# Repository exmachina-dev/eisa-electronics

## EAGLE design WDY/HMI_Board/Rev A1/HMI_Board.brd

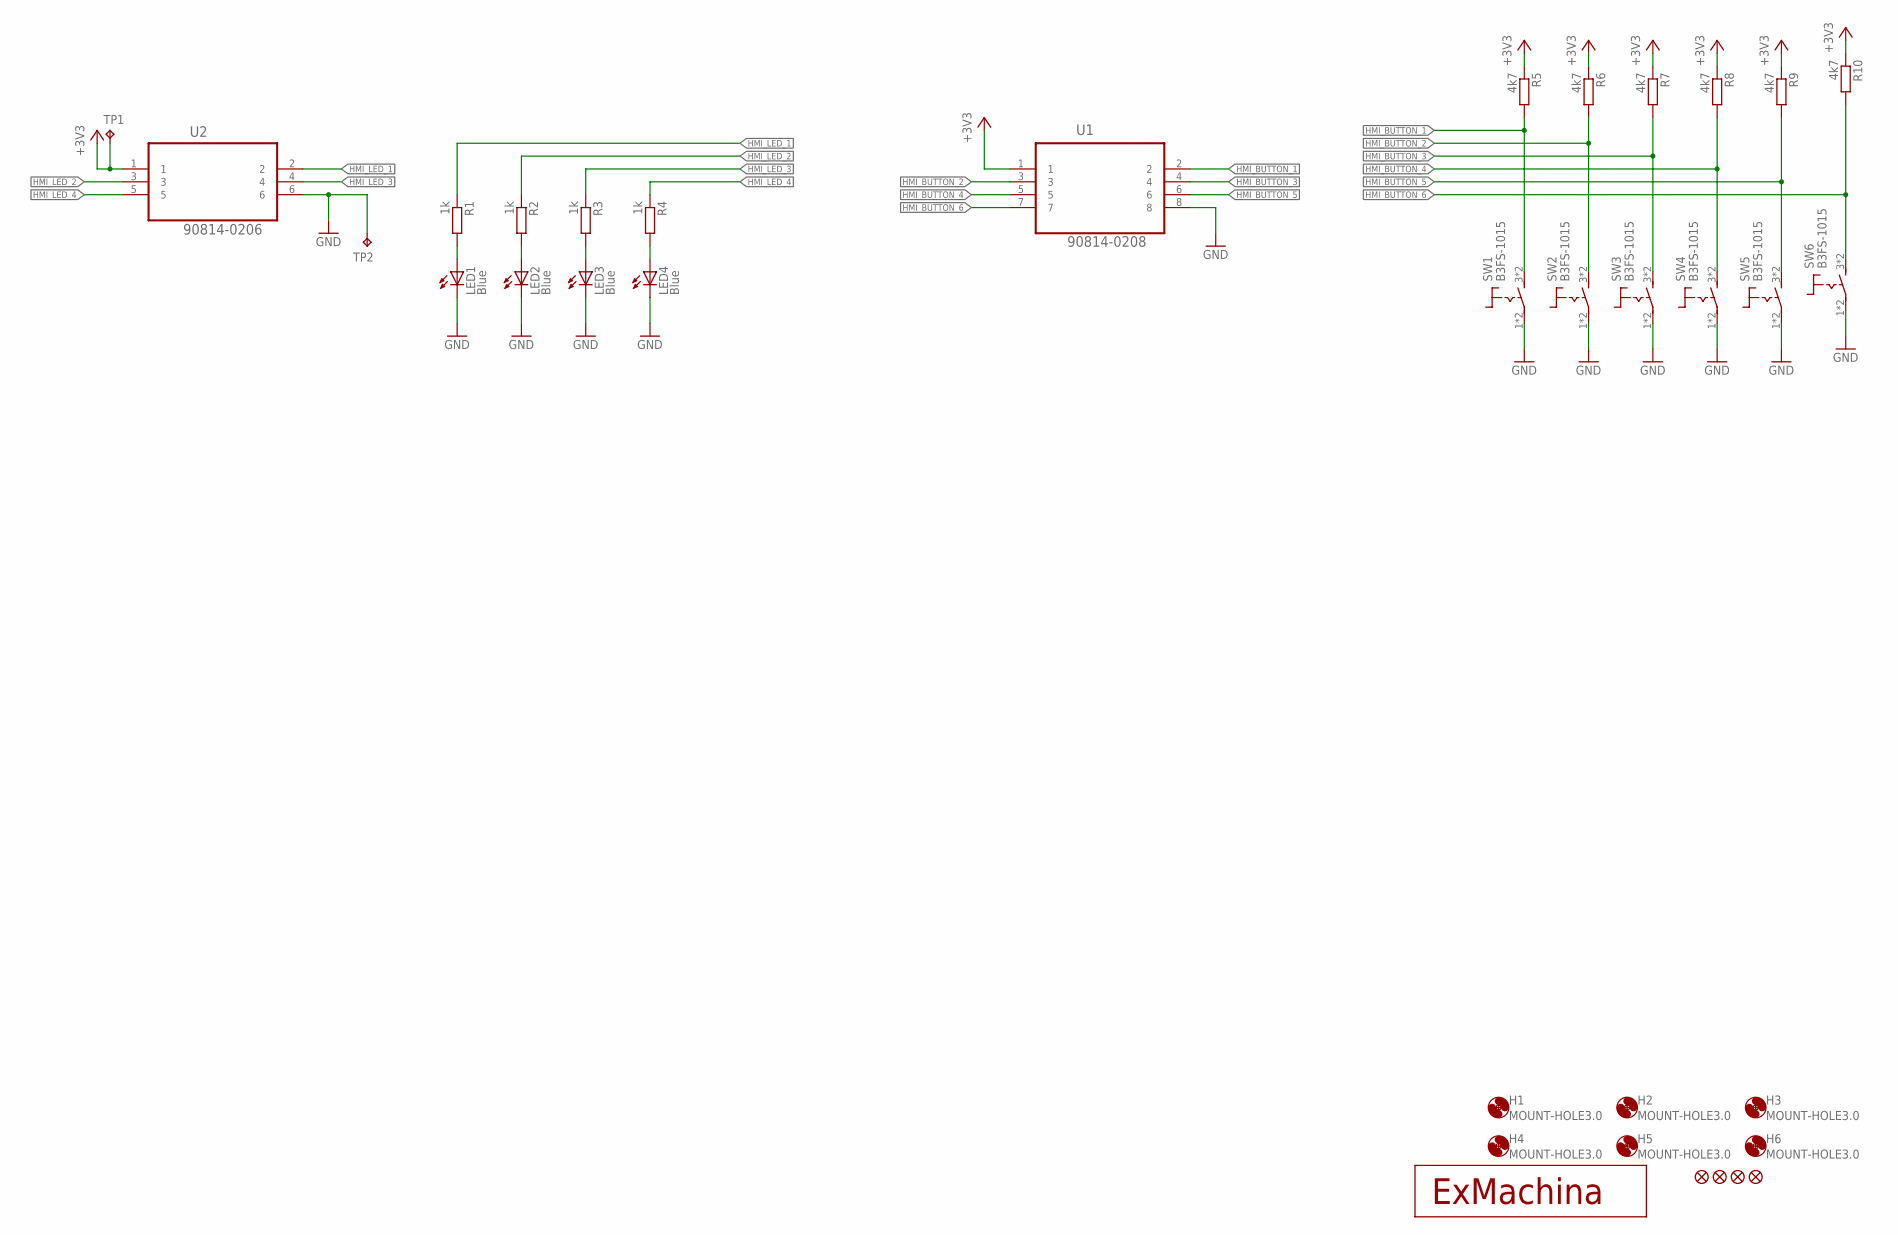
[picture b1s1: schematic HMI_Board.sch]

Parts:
H1, H2, H3, H4, H5, H6: MOUNT-HOLE3.0; 3,0
JP1, JP2, JP3, JP4: FIDUCIAL1X2; FIDUCIAL-1X2
LED1, LED2, LED3, LED4: Blue; SML0603
R1, R2, R3, R4: 1k; R0603
R5, R6, R7, R8, R9, R10: 4k7; R0603
SW1, SW2, SW3, SW4, SW5, SW6: B3FS-1015; B3FS
TP1, TP2: TPB2,54; B2,54
U1: 90814-0208; MOLEX_90814-0208
U2: 90814-0206; MOLEX_90814-0206
U$1: EXMACHINA-LOGO-NAME; EXM-LOGO-BASELINE

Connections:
+3V3: R5.1, R6.1, R7.1, R8.1, R9.1, R10.1, TP1.TP, U1.1, U2.1
GND: LED1.C, LED2.C, LED3.C, LED4.C, SW1.1 (2), SW1.2, SW2.1 (2), SW2.2, SW3.1 (2), SW3.2, SW4.1 (2), SW4.2, SW5.1 (2), SW5.2, SW6.1 (2), SW6.2, TP2.TP, U1.8, U2.6
HMI_BUTTON_1: R5.2, SW1.3 (1), SW1.4 (1), U1.2
HMI_BUTTON_2: R6.2, SW2.3 (1), SW2.4 (1), U1.3
HMI_BUTTON_3: R7.2, SW3.3 (1), SW3.4 (1), U1.4
HMI_BUTTON_4: R8.2, SW4.3 (1), SW4.4 (1), U1.5
HMI_BUTTON_5: R9.2, SW5.3 (1), SW5.4 (1), U1.6
HMI_BUTTON_6: R10.2, SW6.3 (1), SW6.4 (1), U1.7
HMI_LED_1: R1.1, U2.2
HMI_LED_2: R2.1, U2.3
HMI_LED_3: R3.1, U2.4
HMI_LED_4: R4.1, U2.5
unnamed: LED1.A, R1.2
unnamed: LED2.A, R2.2
unnamed: LED3.A, R3.2
unnamed: LED4.A, R4.2

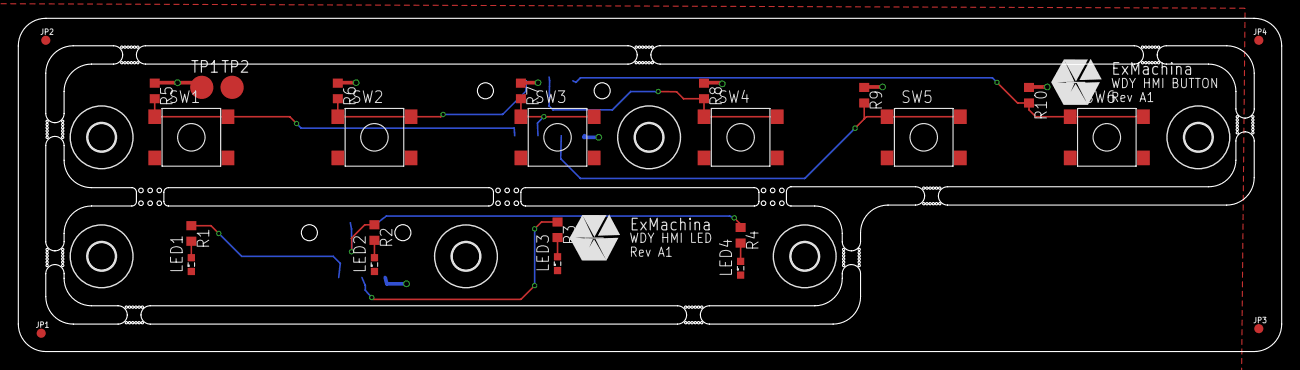
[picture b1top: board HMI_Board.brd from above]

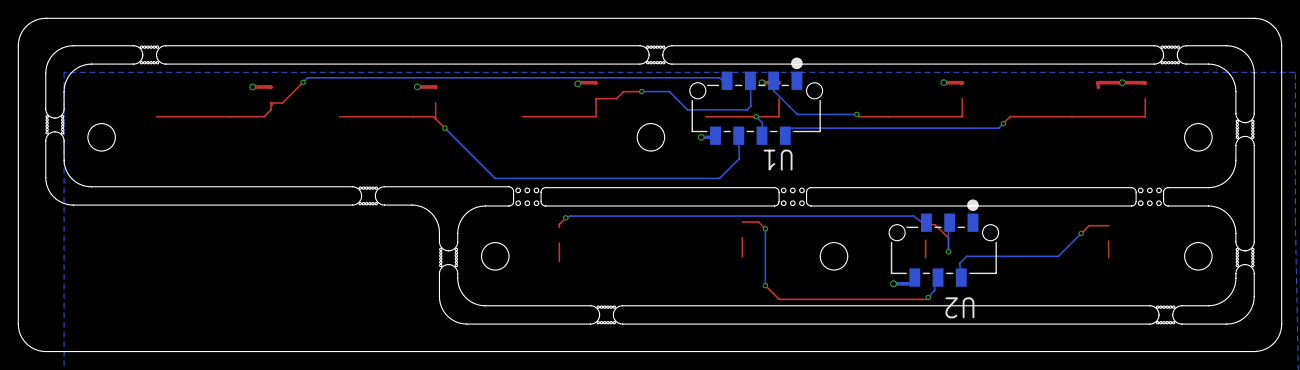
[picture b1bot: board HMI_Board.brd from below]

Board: 2 copper layers, 138.0 x 36.4 mm, 36 parts (2 on the bottom side), 16 nets.

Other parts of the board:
U$2: EXMACHINA-LOGO-NAME; EXM-LOGO-BASELINE

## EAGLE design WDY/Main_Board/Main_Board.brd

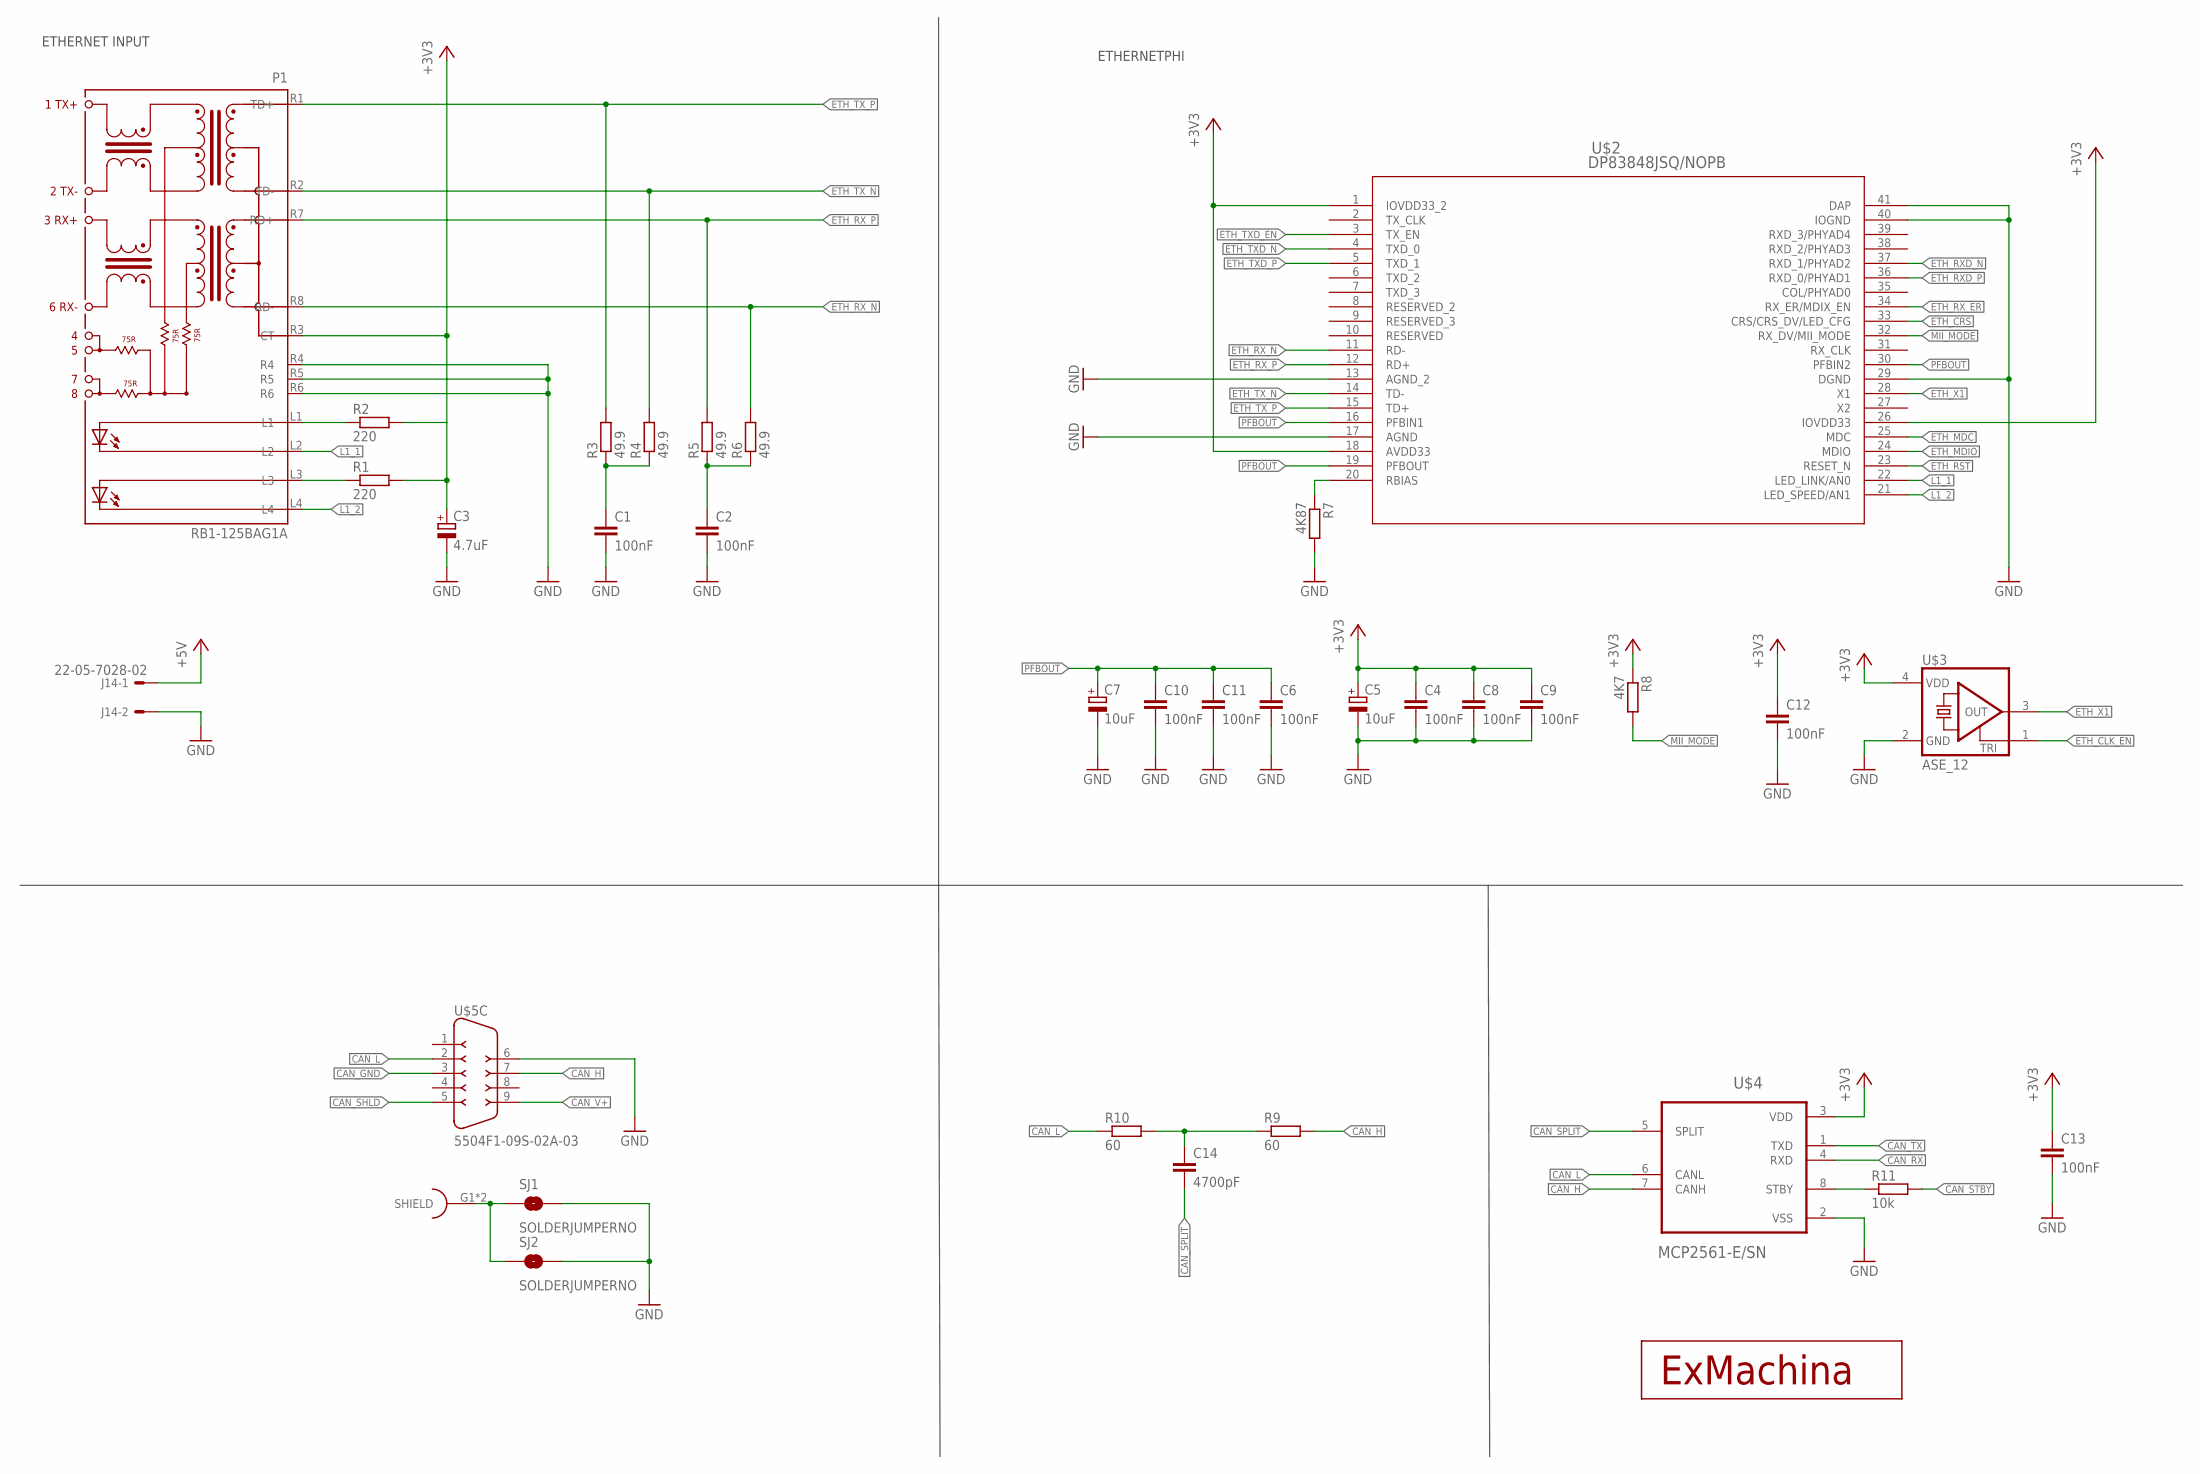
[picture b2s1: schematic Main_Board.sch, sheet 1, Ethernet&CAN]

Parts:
C1, C2, C4, C6, C8, C9, C10, C11, C12, C13: 100nF; C0603
C3: 4.7uF; CT3216
C5, C7: 10uF; CT3216
C14: 4700pF; C0603
J14: 22-05-7028-02; 7395-02
P1: RB1-125BAG1A; WIZNET_RB1-125BAG1A
R1, R2: 220; R0603
R3, R4, R5, R6: 49.9; R0603
R7: 4K87; R0603
R8: 4K7; R0603
R9, R10: 60; R0603
R11: 10k; R0603
SJ1, SJ2: SOLDERJUMPERNO; SJ_2S-NO
U$1: EXMACHINA-LOGO-NAME; EXM-LOGO-BASELINE
U$2: DP83848JSQ/NOPB; SQA40B
U$3: ASE_12; ASE
U$4: MCP2561-E/SN; SOIC127P600X175-8N
U$5: 5504F1-09S-02A-03; 5504F1-09S-02A

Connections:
+3V3: C3.+, C4.1, C5.+, C8.1, C9.1, C12.1, C13.1, P1.R3 (CT), R1.2, R2.2, R8.1, U$2.1 (IOVDD33_2), U$2.18 (AVDD33), U$2.26 (IOVDD33), U$3.4 (VDD), U$4.3 (VDD); also elsewhere on the board
+5V: J14.1; also elsewhere on the board
CAN_GND: U$5.3
CAN_H: R9.2, U$4.7 (CANH), U$5.7
CAN_L: R10.1, U$4.6 (CANL), U$5.2
CAN_RX: U$4.4 (RXD); also elsewhere on the board
CAN_SHLD: U$5.5
CAN_SPLIT: C14.2, U$4.5 (SPLIT)
CAN_STBY: R11.2
CAN_TX: U$4.1 (TXD); also elsewhere on the board
CAN_V+: U$5.9
ETH_CLK_EN: U$3.1 (TRI); also elsewhere on the board
ETH_CRS: U$2.33 (CRS/CRS_DV/LED_CFG); also elsewhere on the board
ETH_MDC: U$2.25 (MDC); also elsewhere on the board
ETH_MDIO: U$2.24 (MDIO); also elsewhere on the board
ETH_RST: U$2.23 (RESET_N)
ETH_RXD_N: U$2.37 (RXD_1/PHYAD2); also elsewhere on the board
ETH_RXD_P: U$2.36 (RXD_0/PHYAD1); also elsewhere on the board
ETH_RX_ER: U$2.34 (RX_ER/MDIX_EN); also elsewhere on the board
ETH_RX_N: P1.R8 (RD-), R6.2, U$2.11 (RD-)
ETH_RX_P: P1.R7 (RD+), R5.2, U$2.12 (RD+)
ETH_TXD_EN: U$2.3 (TX_EN); also elsewhere on the board
ETH_TXD_N: U$2.4 (TXD_0); also elsewhere on the board
ETH_TXD_P: U$2.5 (TXD_1); also elsewhere on the board
ETH_TX_N: P1.R2 (TD-), R4.2, U$2.14 (TD-)
ETH_TX_P: P1.R1 (TD+), R3.2, U$2.15 (TD+)
ETH_X1: U$2.28 (X1), U$3.3 (OUT); also elsewhere on the board
GND: C1.2, C2.2, C3.-, C4.2, C5.-, C6.2, C7.-, C8.2, C9.2, C10.2, C11.2, C12.2, C13.2, J14.2, P1.R4, P1.R5, P1.R6, R7.2, SJ1.2, SJ2.2, U$2.13 (AGND_2), U$2.17 (AGND), U$2.29 (DGND), U$2.40 (IOGND), U$2.41 (DAP), U$3.2 (GND), U$4.2 (VSS), U$5.6; also elsewhere on the board
L1_1: P1.L2, U$2.22 (LED_LINK/AN0)
L1_2: P1.L4, U$2.21 (LED_SPEED/AN1)
MII_MODE: R8.2, U$2.32 (RX_DV/MII_MODE)
unnamed: C1.1, R3.1, R4.1
unnamed: C2.1, R5.1, R6.1
unnamed: C14.1, R9.1, R10.2
unnamed: R7.1, U$2.20 (RBIAS)
unnamed: R11.1, U$4.8 (STBY)
unnamed: SJ1.1, SJ2.1, U$5.G1 (SHIELD), U$5.G2 (SHIELD)
unnamed: P1.L1, R2.1
unnamed: P1.L3, R1.1
PFBOUT: C6.1, C7.+, C10.1, C11.1, U$2.16 (PFBIN1), U$2.19 (PFBOUT), U$2.30 (PFBIN2)

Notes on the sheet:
ETHERNET INPUT
ETHERNETPHI

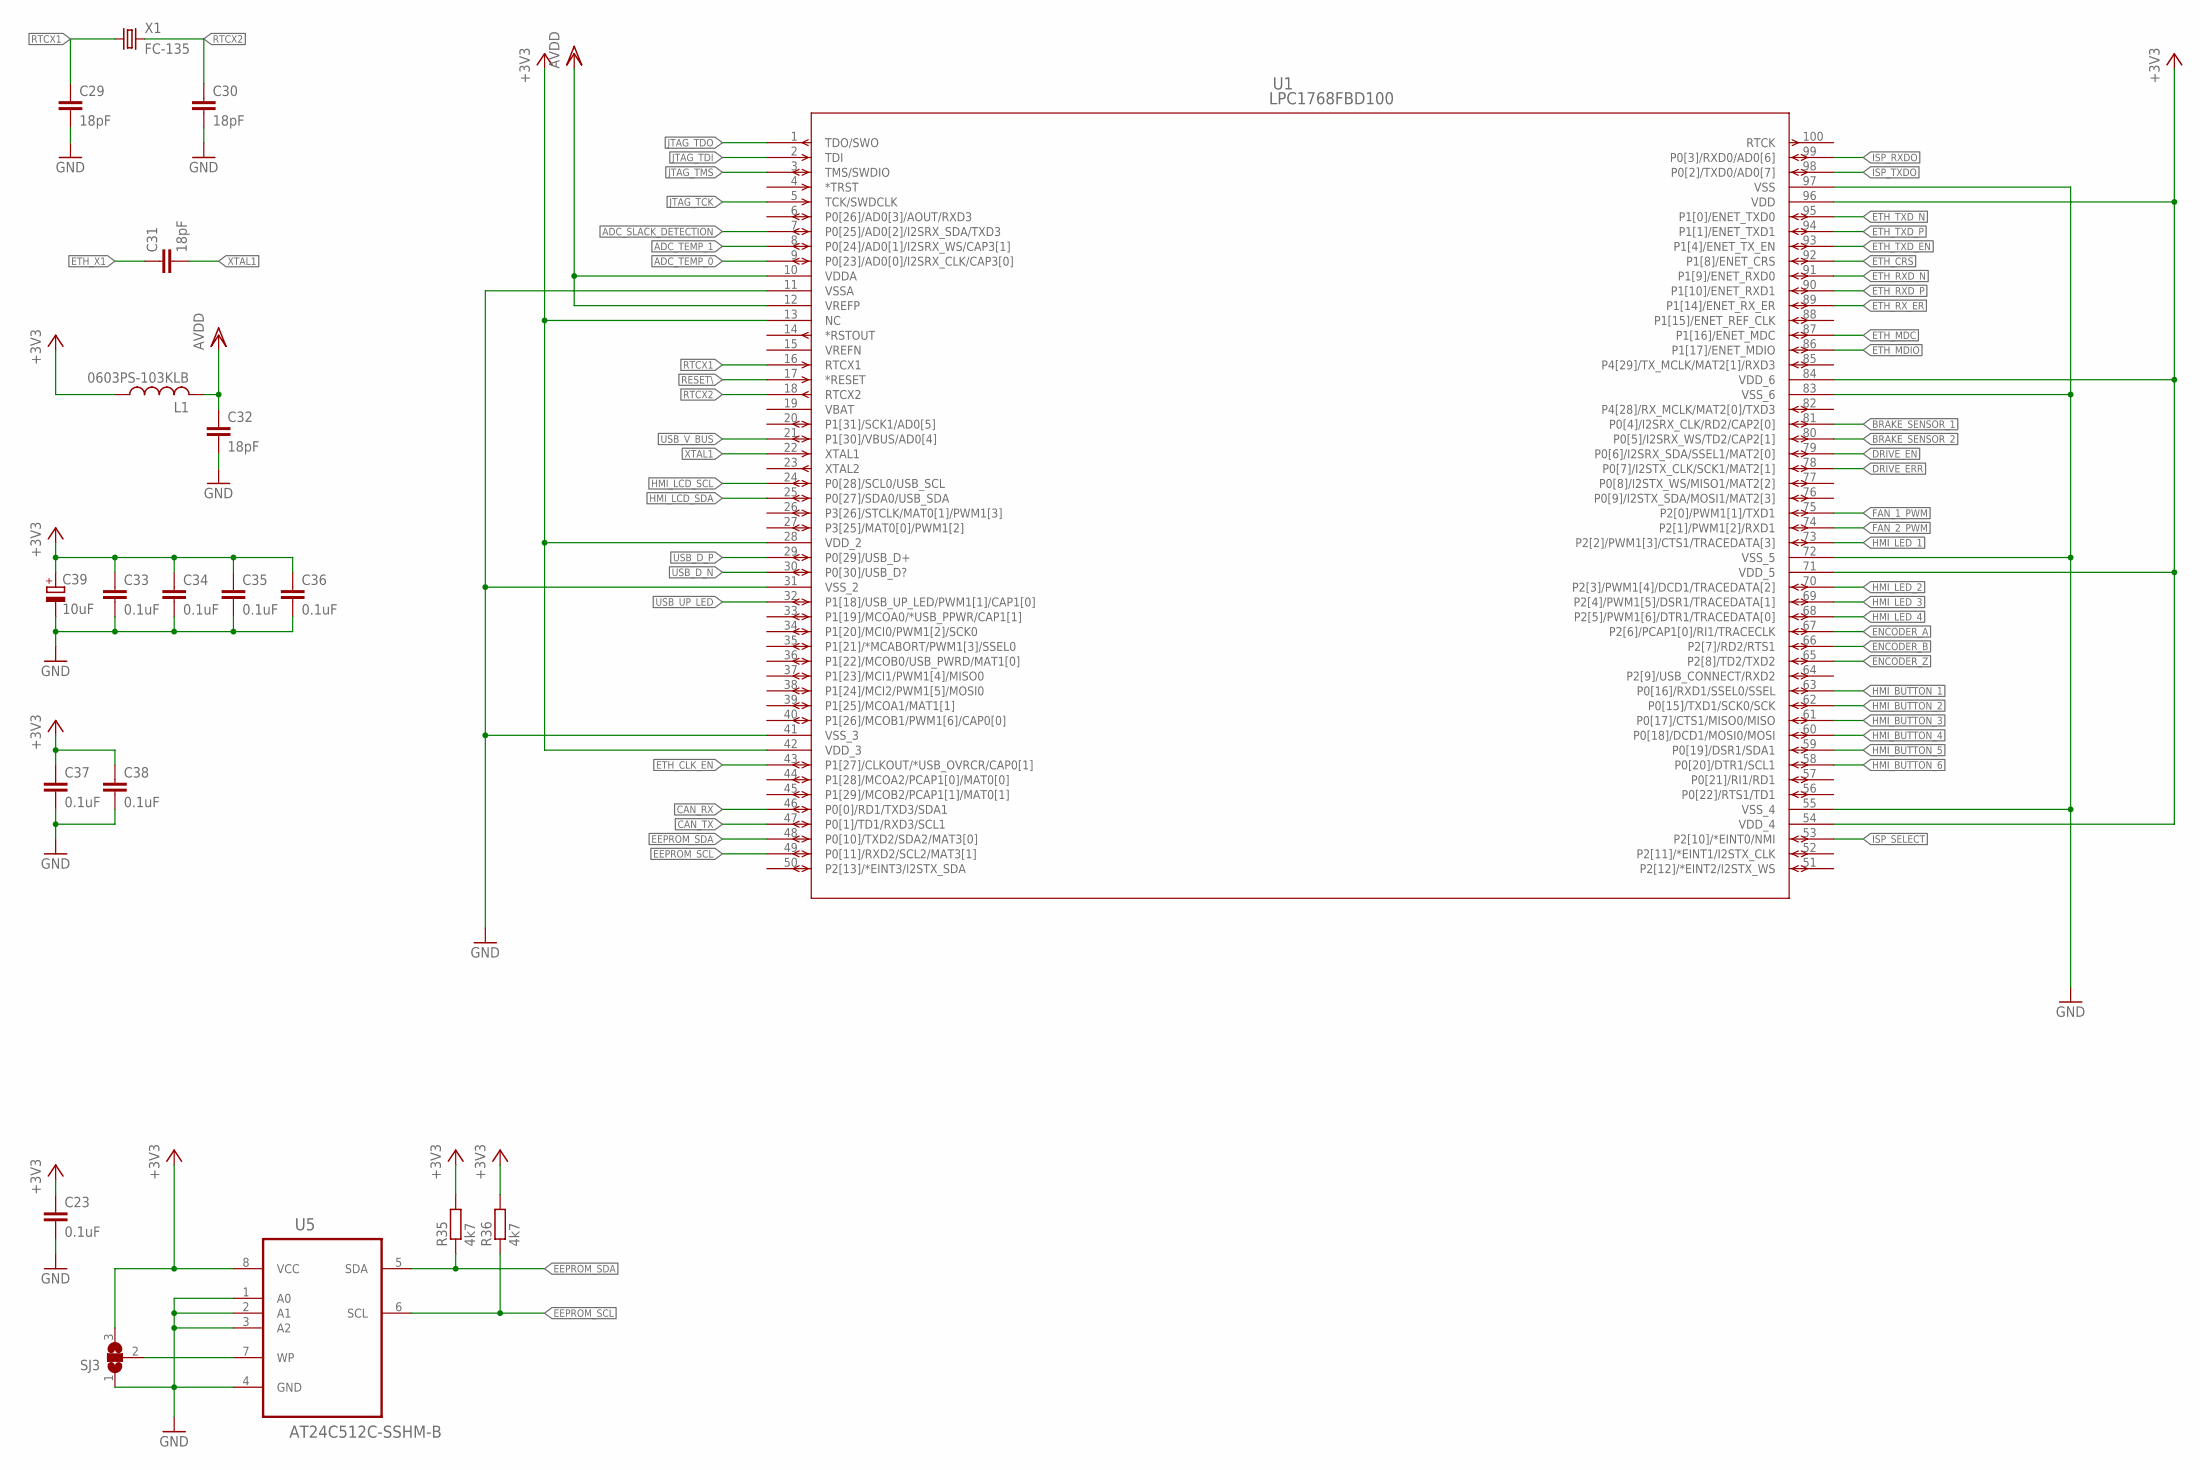
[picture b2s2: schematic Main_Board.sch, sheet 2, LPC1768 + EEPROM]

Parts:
C23, C33, C34, C35, C36, C37, C38: 0.1uF; C0603
C29, C30, C31, C32: 18pF; C0603
C39: 10uF; CT3216
L1: 0603PS-103KLB; 0603
R35, R36: 4k7; R0603
SJ3: SJ2W; SJ_2
U1: LPC1768FBD100; SOT407-1
U5: AT24C512C-SSHM-B; SOIC127P600X175-8N
X1: FC-135

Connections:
+3V3: C23.1, C33.1, C34.1, C35.1, C36.1, C37.1, C38.1, C39.+, L1.P$1 (1), R35.2, R36.2, SJ3.3, U1.13 (NC), U1.28 (VDD_2), U1.42 (VDD_3), U1.54 (VDD_4), U1.71 (VDD_5), U1.84 (VDD_6), U1.96 (VDD), U5.8 (VCC); also elsewhere on the board
ADC_SLACK_DETECTION: U1.7 (P0[25]/AD0[2]/I2SRX_SDA/TXD3); also elsewhere on the board
ADC_TEMP_0: U1.9 (P0[23]/AD0[0]/I2SRX_CLK/CAP3[0]); also elsewhere on the board
ADC_TEMP_1: U1.8 (P0[24]/AD0[1]/I2SRX_WS/CAP3[1]); also elsewhere on the board
AVDD: C32.1, L1.P$2 (2), U1.10 (VDDA), U1.12 (VREFP)
BRAKE_SENSOR_1: U1.81 (P0[4]/I2SRX_CLK/RD2/CAP2[0]); also elsewhere on the board
BRAKE_SENSOR_2: U1.80 (P0[5]/I2SRX_WS/TD2/CAP2[1]); also elsewhere on the board
CAN_RX: U1.46 (P0[0]/RD1/TXD3/SDA1); also elsewhere on the board
CAN_TX: U1.47 (P0[1]/TD1/RXD3/SCL1); also elsewhere on the board
DRIVE_EN: U1.79 (P0[6]/I2SRX_SDA/SSEL1/MAT2[0]); also elsewhere on the board
DRIVE_ERR: U1.78 (P0[7]/I2STX_CLK/SCK1/MAT2[1]); also elsewhere on the board
EEPROM_SCL: R36.1, U1.49 (P0[11]/RXD2/SCL2/MAT3[1]), U5.6 (SCL)
EEPROM_SDA: R35.1, U1.48 (P0[10]/TXD2/SDA2/MAT3[0]), U5.5 (SDA)
ENCODER_A: U1.67 (P2[6]/PCAP1[0]/RI1/TRACECLK); also elsewhere on the board
ENCODER_B: U1.66 (P2[7]/RD2/RTS1); also elsewhere on the board
ENCODER_Z: U1.65 (P2[8]/TD2/TXD2); also elsewhere on the board
ETH_CLK_EN: U1.43 (P1[27]/CLKOUT/*USB_OVRCR/CAP0[1]); also elsewhere on the board
ETH_CRS: U1.92 (P1[8]/ENET_CRS); also elsewhere on the board
ETH_MDC: U1.87 (P1[16]/ENET_MDC); also elsewhere on the board
ETH_MDIO: U1.86 (P1[17]/ENET_MDIO); also elsewhere on the board
ETH_RXD_N: U1.91 (P1[9]/ENET_RXD0); also elsewhere on the board
ETH_RXD_P: U1.90 (P1[10]/ENET_RXD1); also elsewhere on the board
ETH_RX_ER: U1.89 (P1[14]/ENET_RX_ER); also elsewhere on the board
ETH_TXD_EN: U1.93 (P1[4]/ENET_TX_EN); also elsewhere on the board
ETH_TXD_N: U1.95 (P1[0]/ENET_TXD0); also elsewhere on the board
ETH_TXD_P: U1.94 (P1[1]/ENET_TXD1); also elsewhere on the board
ETH_X1: C31.1; also elsewhere on the board
FAN_1_PWM: U1.75 (P2[0]/PWM1[1]/TXD1); also elsewhere on the board
FAN_2_PWM: U1.74 (P2[1]/PWM1[2]/RXD1); also elsewhere on the board
GND: C23.2, C29.2, C30.2, C32.2, C33.2, C34.2, C35.2, C36.2, C37.2, C38.2, C39.-, SJ3.1, U1.11 (VSSA), U1.31 (VSS_2), U1.41 (VSS_3), U1.55 (VSS_4), U1.72 (VSS_5), U1.83 (VSS_6), U1.97 (VSS), U5.1 (A0), U5.2 (A1), U5.3 (A2), U5.4 (GND); also elsewhere on the board
HMI_BUTTON_1: U1.63 (P0[16]/RXD1/SSEL0/SSEL); also elsewhere on the board
HMI_BUTTON_2: U1.62 (P0[15]/TXD1/SCK0/SCK); also elsewhere on the board
HMI_BUTTON_3: U1.61 (P0[17]/CTS1/MISO0/MISO); also elsewhere on the board
HMI_BUTTON_4: U1.60 (P0[18]/DCD1/MOSI0/MOSI); also elsewhere on the board
HMI_BUTTON_5: U1.59 (P0[19]/DSR1/SDA1); also elsewhere on the board
HMI_BUTTON_6: U1.58 (P0[20]/DTR1/SCL1); also elsewhere on the board
HMI_LCD_SCL: U1.24 (P0[28]/SCL0/USB_SCL); also elsewhere on the board
HMI_LCD_SDA: U1.25 (P0[27]/SDA0/USB_SDA); also elsewhere on the board
HMI_LED_1: U1.73 (P2[2]/PWM1[3]/CTS1/TRACEDATA[3]); also elsewhere on the board
HMI_LED_2: U1.70 (P2[3]/PWM1[4]/DCD1/TRACEDATA[2]); also elsewhere on the board
HMI_LED_3: U1.69 (P2[4]/PWM1[5]/DSR1/TRACEDATA[1]); also elsewhere on the board
HMI_LED_4: U1.68 (P2[5]/PWM1[6]/DTR1/TRACEDATA[0]); also elsewhere on the board
ISP_RXDO: U1.99 (P0[3]/RXD0/AD0[6])
ISP_SELECT: U1.53 (P2[10]/*EINT0/NMI)
ISP_TXDO: U1.98 (P0[2]/TXD0/AD0[7])
JTAG_TCK: U1.5 (TCK/SWDCLK); also elsewhere on the board
JTAG_TDI: U1.2 (TDI); also elsewhere on the board
JTAG_TDO: U1.1 (TDO/SWO); also elsewhere on the board
JTAG_TMS: U1.3 (TMS/SWDIO); also elsewhere on the board
unnamed: SJ3.2, U5.7 (WP)
RESET\: U1.17 (*RESET)
RTCX1: C29.1, U1.16 (RTCX1), X1.1
RTCX2: C30.1, U1.18 (RTCX2), X1.2
USB_D_N: U1.30 (P0[30]/USB_D?); also elsewhere on the board
USB_D_P: U1.29 (P0[29]/USB_D+); also elsewhere on the board
USB_UP_LED: U1.32 (P1[18]/USB_UP_LED/PWM1[1]/CAP1[0]); also elsewhere on the board
USB_V_BUS: U1.21 (P1[30]/VBUS/AD0[4]); also elsewhere on the board
VBAT: U1.19 (VBAT)
VREFN: U1.15 (VREFN)
XTAL1: C31.2, U1.22 (XTAL1)

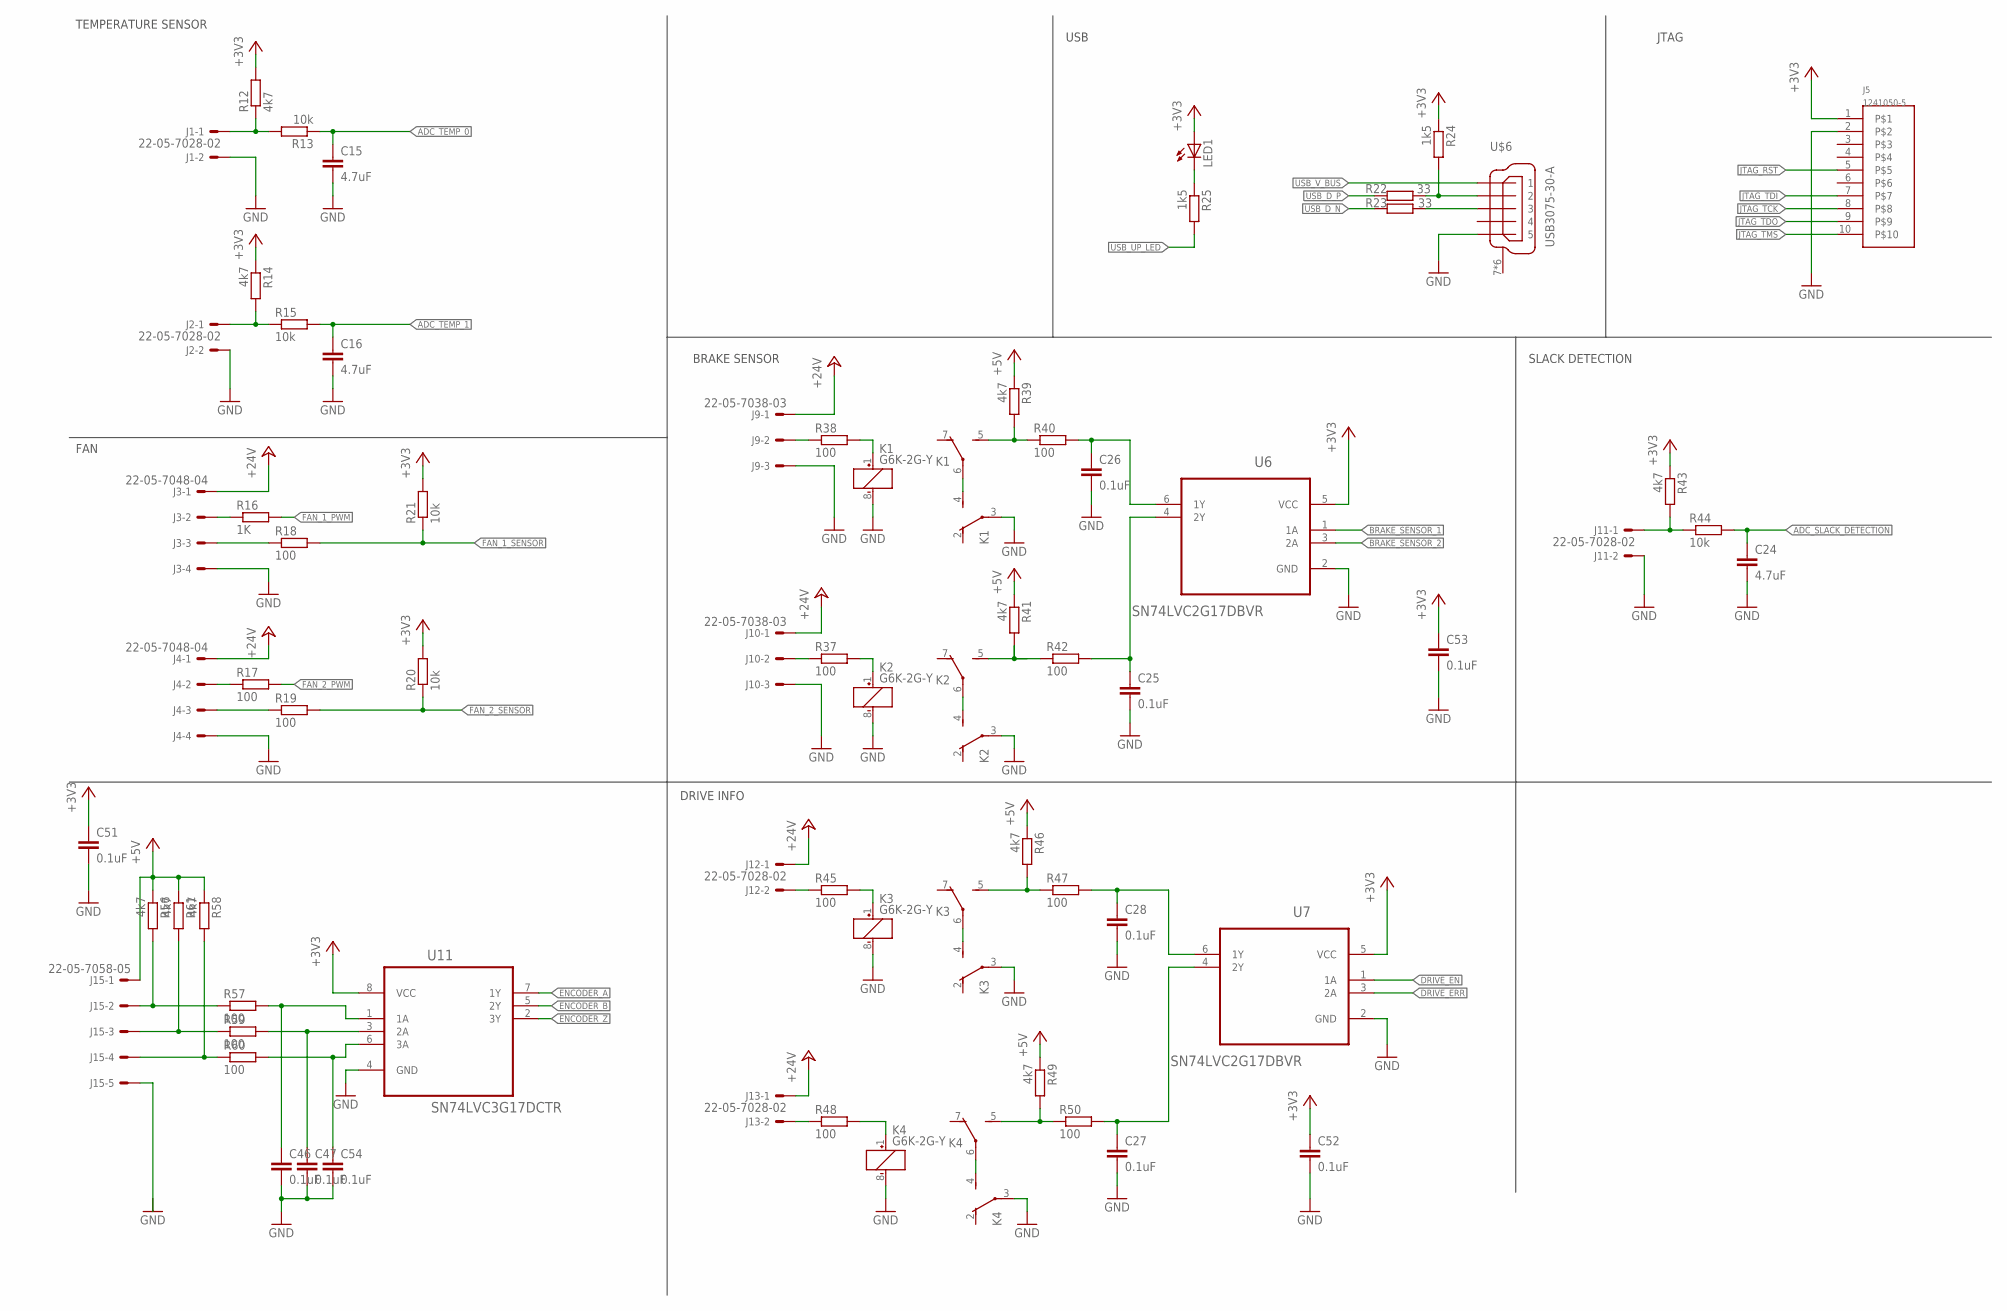
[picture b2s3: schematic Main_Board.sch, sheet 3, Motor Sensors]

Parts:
C15, C16, C24: 4.7uF; C0603
C25, C26, C27, C28, C46, C47, C51, C52, C53, C54: 0.1uF; C0603
J1, J2, J11, J12, J13: 22-05-7028-02; 7395-02
J3, J4: 22-05-7048-04; 7395-04
J5: 1241050-5; 2.54/2X5
J9, J10: 22-05-7038-03; 7395-03
J15: 22-05-7058-05; 7395-05
K1, K2, K3, K4: G6K-2G-Y
LED1: LEDCHIPLED_0603; CHIPLED_0603
R12, R14, R39, R41, R43, R46, R49, R56, R58, R61: 4k7; R0603
R13, R15, R20, R21, R44: 10k; R0603
R16: 1K; R0603
R17, R18, R19, R37, R38, R40, R42, R45, R47, R48, R50, R57, R59, R60: 100; R0603
R22, R23: 33; R0603
R24, R25: 1k5; R0603
U6, U7: SN74LVC2G17DBVR; SOT95P280X145-6N
U11: SN74LVC3G17DCTR; SOP65P400X130-8N
U$6: USB3075-30-A; USB_MICROB_SMT

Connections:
+3V3: C51.1, C52.1, C53.1, J5.1, LED1.A, R12.2, R14.1, R20.2, R21.2, R24.1, R43.1, U6.5 (VCC), U7.5 (VCC), U11.8 (VCC); also elsewhere on the board
+5V: J15.1, R39.1, R41.1, R46.1, R49.1, R56.1, R58.1, R61.1; also elsewhere on the board
+24V: J3.1, J4.1, J9.1, J10.1, J12.1, J13.1; also elsewhere on the board
ADC_SLACK_DETECTION: C24.1, R44.2; also elsewhere on the board
ADC_TEMP_0: C15.1, R13.1; also elsewhere on the board
ADC_TEMP_1: C16.1, R15.2; also elsewhere on the board
BRAKE_SENSOR_1: U6.1 (1A); also elsewhere on the board
BRAKE_SENSOR_2: U6.3 (2A); also elsewhere on the board
DRIVE_EN: U7.1 (1A); also elsewhere on the board
DRIVE_ERR: U7.3 (2A); also elsewhere on the board
ENCODER_A: U11.7 (1Y); also elsewhere on the board
ENCODER_B: U11.5 (2Y); also elsewhere on the board
ENCODER_Z: U11.2 (3Y); also elsewhere on the board
FAN_1_PWM: R16.2; also elsewhere on the board
FAN_1_SENSOR: R18.2, R21.1
FAN_2_PWM: R17.2; also elsewhere on the board
FAN_2_SENSOR: R19.2, R20.1
GND: C15.2, C16.2, C24.2, C25.2, C26.2, C27.2, C28.2, C46.2, C47.2, C51.2, C52.2, C53.2, C54.2, J1.2, J2.2, J3.4, J4.4, J5.2, J9.3, J10.3, J11.2, K1.3, K1.8 (-), K2.3, K2.8 (-), K3.3, K3.8 (-), K4.3, K4.8 (-), U6.2 (GND), U7.2 (GND), U11.4 (GND), U$6.5; also elsewhere on the board
JTAG_RST: J5.5
JTAG_TCK: J5.8; also elsewhere on the board
JTAG_TDI: J5.7; also elsewhere on the board
JTAG_TDO: J5.9; also elsewhere on the board
JTAG_TMS: J5.10; also elsewhere on the board
unnamed: J2.1, R14.2, R15.1
unnamed: J1.1, R12.1, R13.2
unnamed: J3.2, R16.1
unnamed: J4.3, R19.1
unnamed: J4.2, R17.1
unnamed: J3.3, R18.1
unnamed: R22.1, R24.2, U$6.2
unnamed: R23.1, U$6.3
unnamed: LED1.C, R25.1
unnamed: J9.2, R38.1
unnamed: J10.2, R37.1
unnamed: K1.1 (+), R38.2
unnamed: K3.1 (+), R45.2
unnamed: K1.4 (S), K1.6
unnamed: K2.5 (S), R41.2, R42.1
unnamed: J11.1, R43.2, R44.1
unnamed: J12.2, R45.1
unnamed: K4.1 (+), R48.2
unnamed: K3.5 (S), R46.2, R47.1
unnamed: J15.2, R56.2, R57.1
unnamed: K4.5 (S), R49.2, R50.1
unnamed: J13.2, R48.1
unnamed: C25.1, R42.2, U6.4 (2Y)
unnamed: C26.1, R40.2, U6.6 (1Y)
unnamed: J15.3, R59.1, R61.2
unnamed: C28.1, R47.2, U7.6 (1Y)
unnamed: C27.1, R50.2, U7.4 (2Y)
unnamed: J15.4, R58.2, R60.1
unnamed: C54.1, R60.2, U11.6 (3A)
unnamed: C47.1, R59.2, U11.3 (2A)
unnamed: C46.1, R57.2, U11.1 (1A)
unnamed: K2.1 (+), R37.2
unnamed: K2.4 (S), K2.6
unnamed: K1.5 (S), R39.2, R40.1
unnamed: K4.4 (S), K4.6
unnamed: K3.4 (S), K3.6
USB_D_N: R23.2; also elsewhere on the board
USB_D_P: R22.2; also elsewhere on the board
USB_UP_LED: R25.2; also elsewhere on the board
USB_V_BUS: U$6.1; also elsewhere on the board

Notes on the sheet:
USB
JTAG
TEMPERATURE SENSOR
FAN
SLACK DETECTION
BRAKE SENSOR
DRIVE INFO

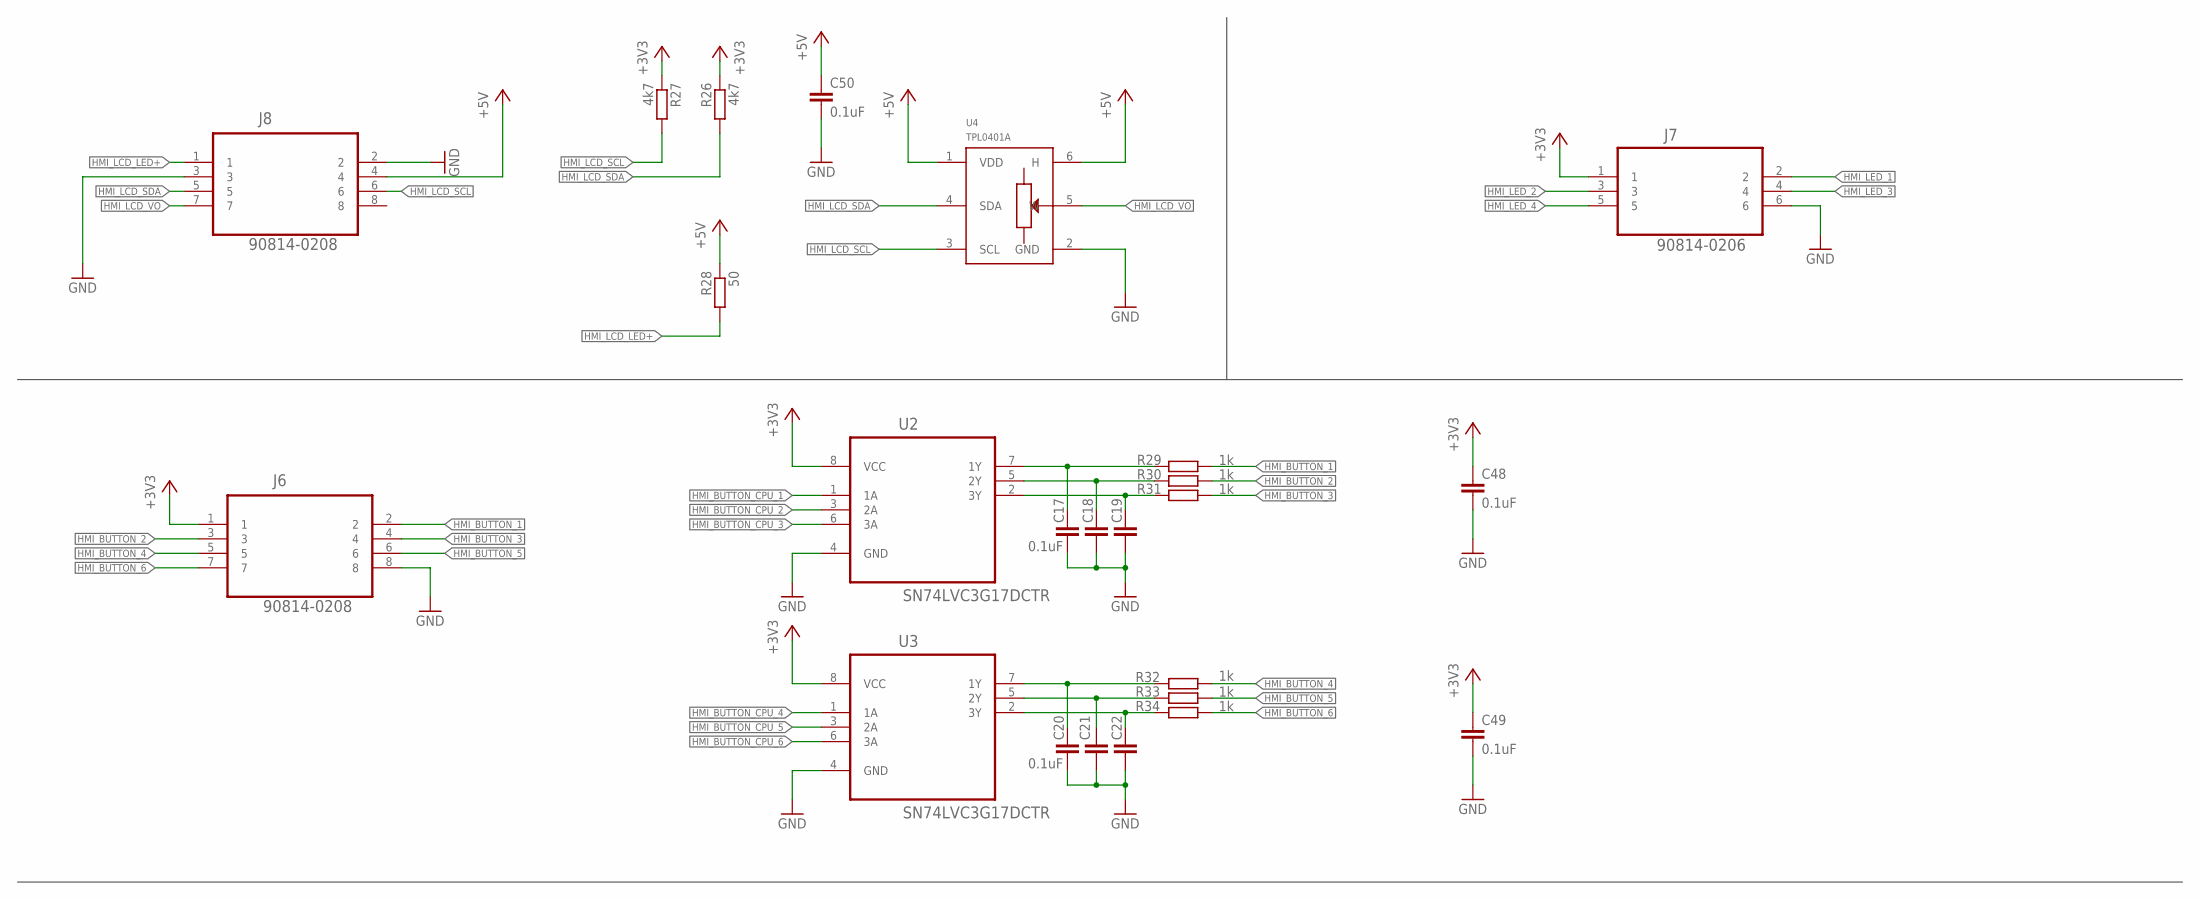
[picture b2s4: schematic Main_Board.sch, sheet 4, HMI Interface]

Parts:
C17, C18, C19, C20, C21, C22, C48, C49, C50: 0.1uF; C0603
J6, J8: 90814-0208; MOLEX_90814-0208
J7: 90814-0206; MOLEX_90814-0206
R26, R27: 4k7; R0603
R28: 50; R0603
R29, R30, R31, R32, R33, R34: 1k; R0603
U2, U3: SN74LVC3G17DCTR; SOP65P400X130-8N
U4: TPL0401A; SC-70-DCK

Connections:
+3V3: C48.1, C49.1, J6.1, J7.1, R26.1, R27.1, U2.8 (VCC), U3.8 (VCC); also elsewhere on the board
+5V: C50.1, J8.4, R28.1, U4.1 (VDD), U4.6 (H); also elsewhere on the board
GND: C17.2, C18.2, C19.2, C20.2, C21.2, C22.2, C48.2, C49.2, C50.2, J6.8, J7.6, J8.2, J8.3, U2.4 (GND), U3.4 (GND), U4.2 (GND); also elsewhere on the board
HMI_BUTTON_1: J6.2, R29.1; also elsewhere on the board
HMI_BUTTON_2: J6.3, R30.1; also elsewhere on the board
HMI_BUTTON_3: J6.4, R31.1; also elsewhere on the board
HMI_BUTTON_4: J6.5, R32.1; also elsewhere on the board
HMI_BUTTON_5: J6.6, R33.1; also elsewhere on the board
HMI_BUTTON_6: J6.7, R34.1; also elsewhere on the board
HMI_BUTTON_CPU_1: U2.1 (1A)
HMI_BUTTON_CPU_2: U2.3 (2A)
HMI_BUTTON_CPU_3: U2.6 (3A)
HMI_BUTTON_CPU_4: U3.1 (1A)
HMI_BUTTON_CPU_5: U3.3 (2A)
HMI_BUTTON_CPU_6: U3.6 (3A)
HMI_LCD_LED+: J8.1, R28.2
HMI_LCD_SCL: J8.6, R27.2, U4.3 (SCL); also elsewhere on the board
HMI_LCD_SDA: J8.5, R26.2, U4.4 (SDA); also elsewhere on the board
HMI_LCD_VO: J8.7, U4.5 (W)
HMI_LED_1: J7.2; also elsewhere on the board
HMI_LED_2: J7.3; also elsewhere on the board
HMI_LED_3: J7.4; also elsewhere on the board
HMI_LED_4: J7.5; also elsewhere on the board
unnamed: C17.1, R29.2, U2.7 (1Y)
unnamed: C18.1, R30.2, U2.5 (2Y)
unnamed: C19.1, R31.2, U2.2 (3Y)
unnamed: C20.1, R32.2, U3.7 (1Y)
unnamed: C21.1, R33.2, U3.5 (2Y)
unnamed: C22.1, R34.2, U3.2 (3Y)

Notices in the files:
parts and their libraries:
COPYRIGHT: Copyright (C) 2015 Accelerated Designs. All rights reserved
Wurth-POWER_MAGNETICS-rev16f: Copyright: Würth Elektronik
